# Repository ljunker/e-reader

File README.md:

# DIY e-reader

A pocket e-reader built around a **Waveshare 4.2" e-Paper Module V2** (400 × 300, black/white + 4 grays),
an **ESP32-S3** (Unexpected Maker FeatherS3[D], 16 MB flash / 8 MB PSRAM), a microSD card and a 3D-printed case.
It reads books in portrait at 300 × 400, sleeps between page turns and runs for weeks on a 1500–2000 mAh LiPo.

| | |
|---|---|
| **Formats** | `.txt`; **EPUB** laid out on the device (bold/italic, headings, pictures, table of contents); **PDF / comics** pre-rendered on your computer with [`xtconvert`](tools/converter) into `.xtp` |
| **Controls** | PREV / NEXT on the grip edge (left by default, `left_handed` in `cad/params.scad`), MENU / OK / BACK below the screen; long press jumps 10 pages |
| **Getting books on** | microSD card, Wi‑Fi upload page in the browser, USB drive over USB‑C, or straight from an OPDS catalog (Calibre content server, Project Gutenberg …) |
| **Case** | ~95 × 137 × 17 mm, parametric OpenSCAD, fits a Bambu A1 mini |

## Repository
| Folder | What's inside |
|---|---|
| [`hardware/`](hardware) | [Bill of materials](hardware/BOM.md), [wiring](hardware/wiring.md) |
| [`cad/`](cad) | OpenSCAD case: `params.scad` holds every dimension; `make` exports STLs and runs a collision check |
| [`firmware/`](firmware) | PlatformIO project (Arduino on ESP32-S3) |
| [`tools/converter/`](tools/converter) | `xtconvert`: PDF / CBZ / images → `.xtp` |
| [`docs/`](docs) | [Assembly](docs/assembly.md), [printing](docs/printing.md) |

## Quick start
1. Buy the parts in the [BOM](hardware/BOM.md) and wire them per [wiring.md](hardware/wiring.md) (breadboard first).
2. Flash the firmware:
   ```bash
   cd firmware && pio run -t upload
   ```
3. Format a microSD card as FAT32, make a `books/` folder and copy `.epub` and `.txt` files and converted PDFs into it:
   ```bash
   cd tools/converter && uv run xtconvert ~/Downloads/paper.pdf --mode width -o /Volumes/SD/books/
   ```
4. Measure your display module, set the values in `cad/params.scad`, print the fit test, then the case ([printing.md](docs/printing.md)).
5. Assemble ([assembly.md](docs/assembly.md)).

## Development
```bash
cd firmware && pio test -e native          # panel model, layout, EPUB, zip, image and .xtp unit tests on your computer
cd tools/converter && uv run pytest        # converter tests
make -C cad                                # STLs + collision check (needs OpenSCAD 2024+)
make -C cad png                            # preview renders
make -C cad steps                          # step-by-step pictures for docs/assembly.md
```

## Simulator
Try the firmware in the browser, without hardware:
```bash
brew install emscripten                 # once (or https://emscripten.org)
cd firmware && pio run -e sim -t serve  # then open http://localhost:8000/
```
`env:sim` compiles everything in `src/` unchanged, with the real GxEPD2, Adafruit GFX and U8g2 libraries
and String/FS from the arduino-esp32 core, to WebAssembly. Only the hardware underneath is simulated (`firmware/sim/`):
- **Display:** an SSD1683 model (`lib/epdsim`) receives GxEPD2's SPI commands and the reader's 4-gray refresh. It holds
  BUSY for the real refresh time and shows full refreshes flashing, like the panel does. "Instant refresh" skips the wait.
- **Buttons:** click the caps or use the keys ← PREV, → NEXT, M MENU, Enter OK, Esc BACK. Holding a button gives a
  long press.
- **microSD and NVS:** kept in the browser's IndexedDB. On first start the card gets the test EPUBs, a short TXT and a
  `wifi.txt`. The side panel lists, adds, downloads and deletes files.
- **Deep sleep:** "Skip 3 min" runs out the idle timer. The panel keeps its picture, and a button reboots the
  firmware with its RTC memory, as on the chip. "Reset" is a cold start.
- **USB-C:** set the cable to Unplugged, Computer or Charger. While the drive is on, the file panel is the computer's
  view, and "Eject" ejects it.
- **Wi‑Fi:** the firmware's own upload page appears in the side panel. A service worker passes its requests to the
  firmware's web server.
- **Online library:** the card gets an `opds.txt` for a demo catalog of the sample books that `serve.py` serves,
  behind Digest login like Calibre (user and password `demo`). The firmware's HTTP requests go through
  `serve.py`'s `/proxy`, so real catalogs (your Calibre server, Gutenberg) work too. "Edit opds.txt" changes the list.
- **Battery:** a simulated MAX17048 on I2C, set with the slider.

Not simulated: radio, real USB/sector access, RAM/PSRAM limits and the speed of the ESP32-S3 (EPUB conversion is
much faster in the browser).

## EPUB on the device
The first time a book is opened, the reader converts it once into cache files in `/.reader/` on the card
(this takes a few seconds to about a minute with many pictures; the panel shows the progress).
After that, opening, turning pages and changing the font size are as fast as with `.txt` files.
MENU → **Contents** jumps to a chapter.

**Hyphenation:** copy the [`sdcard/hyph/`](sdcard/hyph) folder to the top of the card (`/hyph/de.hyp`, `/hyph/en.hyp`).
Long words are then broken at line ends, so justified lines get even gaps. The language comes from the EPUB's
`dc:language`; for TXT files and EPUBs without it the reader guesses German or English from the text. Other
languages and a card without `/hyph/` still break after hyphens already in a word ("E-Mail-Adresse").
MENU → **Hyphenation** switches it off. Built with `xtconvert hyph` from the hyph-utf8 patterns in
`tools/converter/patterns/`. Updating to this firmware converts each EPUB once more on first open.

**Fonts:** copy the [`sdcard/fonts/`](sdcard/fonts) folder to the top of the card (`/fonts/literata.xff`).
Books are then set in Literata (regular, bold, italic, bold italic) with true quotes and dashes; menus always use the
built-in Inter, which also stands in for books when the card has no fonts. MENU → **Font** switches between the
families in `/fonts/`. Your own TTF/OTF fonts: `xtconvert font` ([tools/converter](tools/converter#fonts)).

Supported: EPUB 2 and 3, chapters in reading order, headings, bold and italic, alignment, blockquotes,
lists, line breaks, page breaks from CSS, JPEG (baseline) and PNG pictures dithered to the panel,
and the table of contents from the nav document or the NCX.
Not supported: DRM-protected books (the reader says so), GIF/SVG and progressive JPEG pictures (left out),
characters outside Latin-1 and the usual punctuation (shown as the nearest Latin letter or `?`), footnote pop-ups.

## Wi‑Fi upload & USB drive
**Wi‑Fi:** put a `wifi.txt` in the top folder of the card, one network per line:
```
# SSID = password   (lines starting with # are ignored)
Zuhause = geheim123
Büro WLAN = pass=word
Gartenhaus =
```
The line is split at the first `=`, so the password may contain `=` or `#`; leave it empty for an open network.
MENU → **Wi‑Fi upload** joins the strongest of these networks and shows the address.
Open `http://ereader.local/` (or the IP shown) in a browser on the same network to upload, replace or delete books;
the screen counts the files that arrive. BACK switches Wi‑Fi off, and so do 10 minutes without a request.

**USB:** plug the reader into a computer with the USB‑C cable. It asks whether to show the card as a USB drive
(OK) or to keep reading (BACK); MENU → **USB drive** offers it again. Copy books into `books/`, eject the drive,
and the reader returns to the library. A charger alone never triggers the question.

The firmware uses its own partition table (`firmware/partitions-16MB.csv`: two 4 MB app slots, TinyUF2, FAT); the first
`pio run -t upload` after updating rewrites it. Saved reading positions stay.

## Online library (OPDS / Calibre)
Browse an OPDS catalog on the reader and download books straight into `books/`. Put an `opds.txt` next to
`wifi.txt` in the top folder of the card, one catalog per line:
```
# Name = URL   (user and password go into the URL; add "insecure" for a self-signed HTTPS server)
Calibre = http://leser:geheim@192.168.1.10:8080/opds
Project Gutenberg = https://www.gutenberg.org/ebooks.opds/
```
MENU → **Online library** joins the Wi‑Fi from `wifi.txt` and opens the catalog (with several, it asks which).
PREV/NEXT move, OK opens a folder or a book, BACK goes up a level and, at the top, switches Wi‑Fi off; MENU
leaves straight away. A book shows its author, size and description; OK downloads it as
`books/<Title> - <Author>.epub` (or `.txt`), and OK again opens it. "More …" at the end of a list loads the next
page. Ten minutes without a button switch Wi‑Fi off.

**Calibre:** start the content server (Preferences → Sharing over the net, or
`calibre-server --listen-on 0.0.0.0 ~/Calibre\ Library`); the catalog is at `http://<computer>:8080/opds`.
With "Require username and password" on, put them into the URL as above (percent-encode `@`, `:` and `/` in
them). Both of Calibre's login methods work (Digest over HTTP, Basic over HTTPS). The reader sends them only to the
catalog's own server, and only after it asks.

Works with OPDS 1.x (Atom) catalogs; EPUB is taken first, then plain text. Books offered only as MOBI, PDF or
AZW are listed but cannot be downloaded. No search (there is no keyboard), and OPDS 2 (JSON) catalogs are not supported.

## Status / roadmap
- [x] Hardware design, wiring, BOM
- [x] Parametric case with collision check
- [x] PDF/comic converter and `.xtp` format
- [x] Firmware: display, buttons, SD, deep sleep + wake on any button, library, TXT reader with justified text and cached pagination, `.xtp` viewer, font sizes, saved positions
- [ ] Bring-up on real hardware (FeatherS3[D] pin check, Rev2.2 `PWR` pin, rotation, fuel gauge, card detect polarity)
- [x] Fonts generated from TTFs (`xtconvert font`, loaded from the card), shown in black and white
- [x] Hyphenation (Liang patterns, German and English)
- [x] EPUB (unzip, OPF/spine, XHTML + CSS subset, images, table of contents)
- [x] True 4-gray refresh for `.xtp` pages and the sleep-screen cover (about 5.5 s per refresh)
- [x] Wi‑Fi upload page, USB mass storage
- [x] Online library: OPDS catalogs (Calibre content server) over HTTP and HTTPS
- [ ] Optional KiCad carrier PCB (draft in tag `carrier-pcb-draft`)

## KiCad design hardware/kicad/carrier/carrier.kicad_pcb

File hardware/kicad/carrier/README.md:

# Carrier board

A 2-layer board (88.5 × 130 mm, 1.6 mm) that replaces the hand wiring. It takes the
place of the old chassis plate: it sits behind the display, clamped between the
front frame's screw bosses and the back shell.

| Back side (towards the back shell) | Front side (towards the display) |
|---|---|
|  |  |

- **Back side:** FeatherS3 on plain pin headers, microSD socket (card goes in through the
  right side wall), page-turn buttons at the right edge, power switch (top edge),
  battery connector, 1×9 header for the display cable.
- **Front side:** MENU / OK / BACK buttons under the screen.
- GND pour on both layers, 0.25 mm signal and 0.5 mm power tracks, nothing finer than 0.15 mm.
- The GPIO assignment is the same as in [`wiring.md`](../../wiring.md), so the firmware is unchanged.

## Ordering (JLCPCB or similar)
Upload [`fab/carrier-gerbers.zip`](fab/carrier-gerbers.zip). Settings: 2 layers, 1.6 mm FR-4,
HASL lead-free or ENIG, any solder mask colour; all other settings default. No assembly
needed; everything is hand-solderable. Parts: [`fab/carrier-bom.csv`](fab/carrier-bom.csv)
and the [project BOM](../../BOM.md).

Schematic: [`fab/carrier-schematic.pdf`](fab/carrier-schematic.pdf).
3D model for checking against the case: `fab/carrier.step`.

## Soldering order
1. microSD socket J1 (1.1 mm pitch; tack one shield pad, align, then the rest), R1–R5, C1, C2.
2. Front buttons SW1–SW3 on the **front** side, side buttons SW4/SW5, power switch SW6,
   battery connector J2, display header J3 on the **back** side.
3. FeatherS3: put the 16- and 12-pin headers into the board (plastic spacer on the back side),
   put the Feather on top and solder both ends.
4. Trim all through-hole leads on the **display side** to ≤ 1 mm and cover them with Kapton
   tape. The display sits 3 mm away.

## Before ordering, check against the real parts
- **microSD orientation:** the card is assumed to go in on the footprint's +Y side (Molex 104031-0811).
  Compare with the datasheet drawing.
- **Side buttons:** `side_act_h` (actuator height above the board, 3.5 mm) in `cad/params.scad`
  must match the switch you buy. It sets the height of the button holes.
- **FeatherS3 header:** the two Feather pins that the board leaves unused (3 and 16) are only
  marked "unconnected" here, so their exact function on the FeatherS3 doesn't matter.

## Regenerating
Everything is generated from [`design.py`](design.py) (parts, nets, placement) and
`cad/params.scad` (outline, button and connector positions). Don't edit the KiCad files by hand;
change the sources and run:

```bash
make            # place + autoroute (Freerouting), schematic, ERC/DRC/parity check, fab outputs
make pcb        # only place + route
make check      # ERC, DRC with schematic parity
```

Needs KiCad 10 (its bundled Python runs `generate_pcb.py` and `route.py`), Java 17+ and the
GitHub CLI (fetches Freerouting into `.tools/` on first use). Freerouting's result varies
between runs, so `route.py` retries up to 5 times until KiCad reports every connection made.

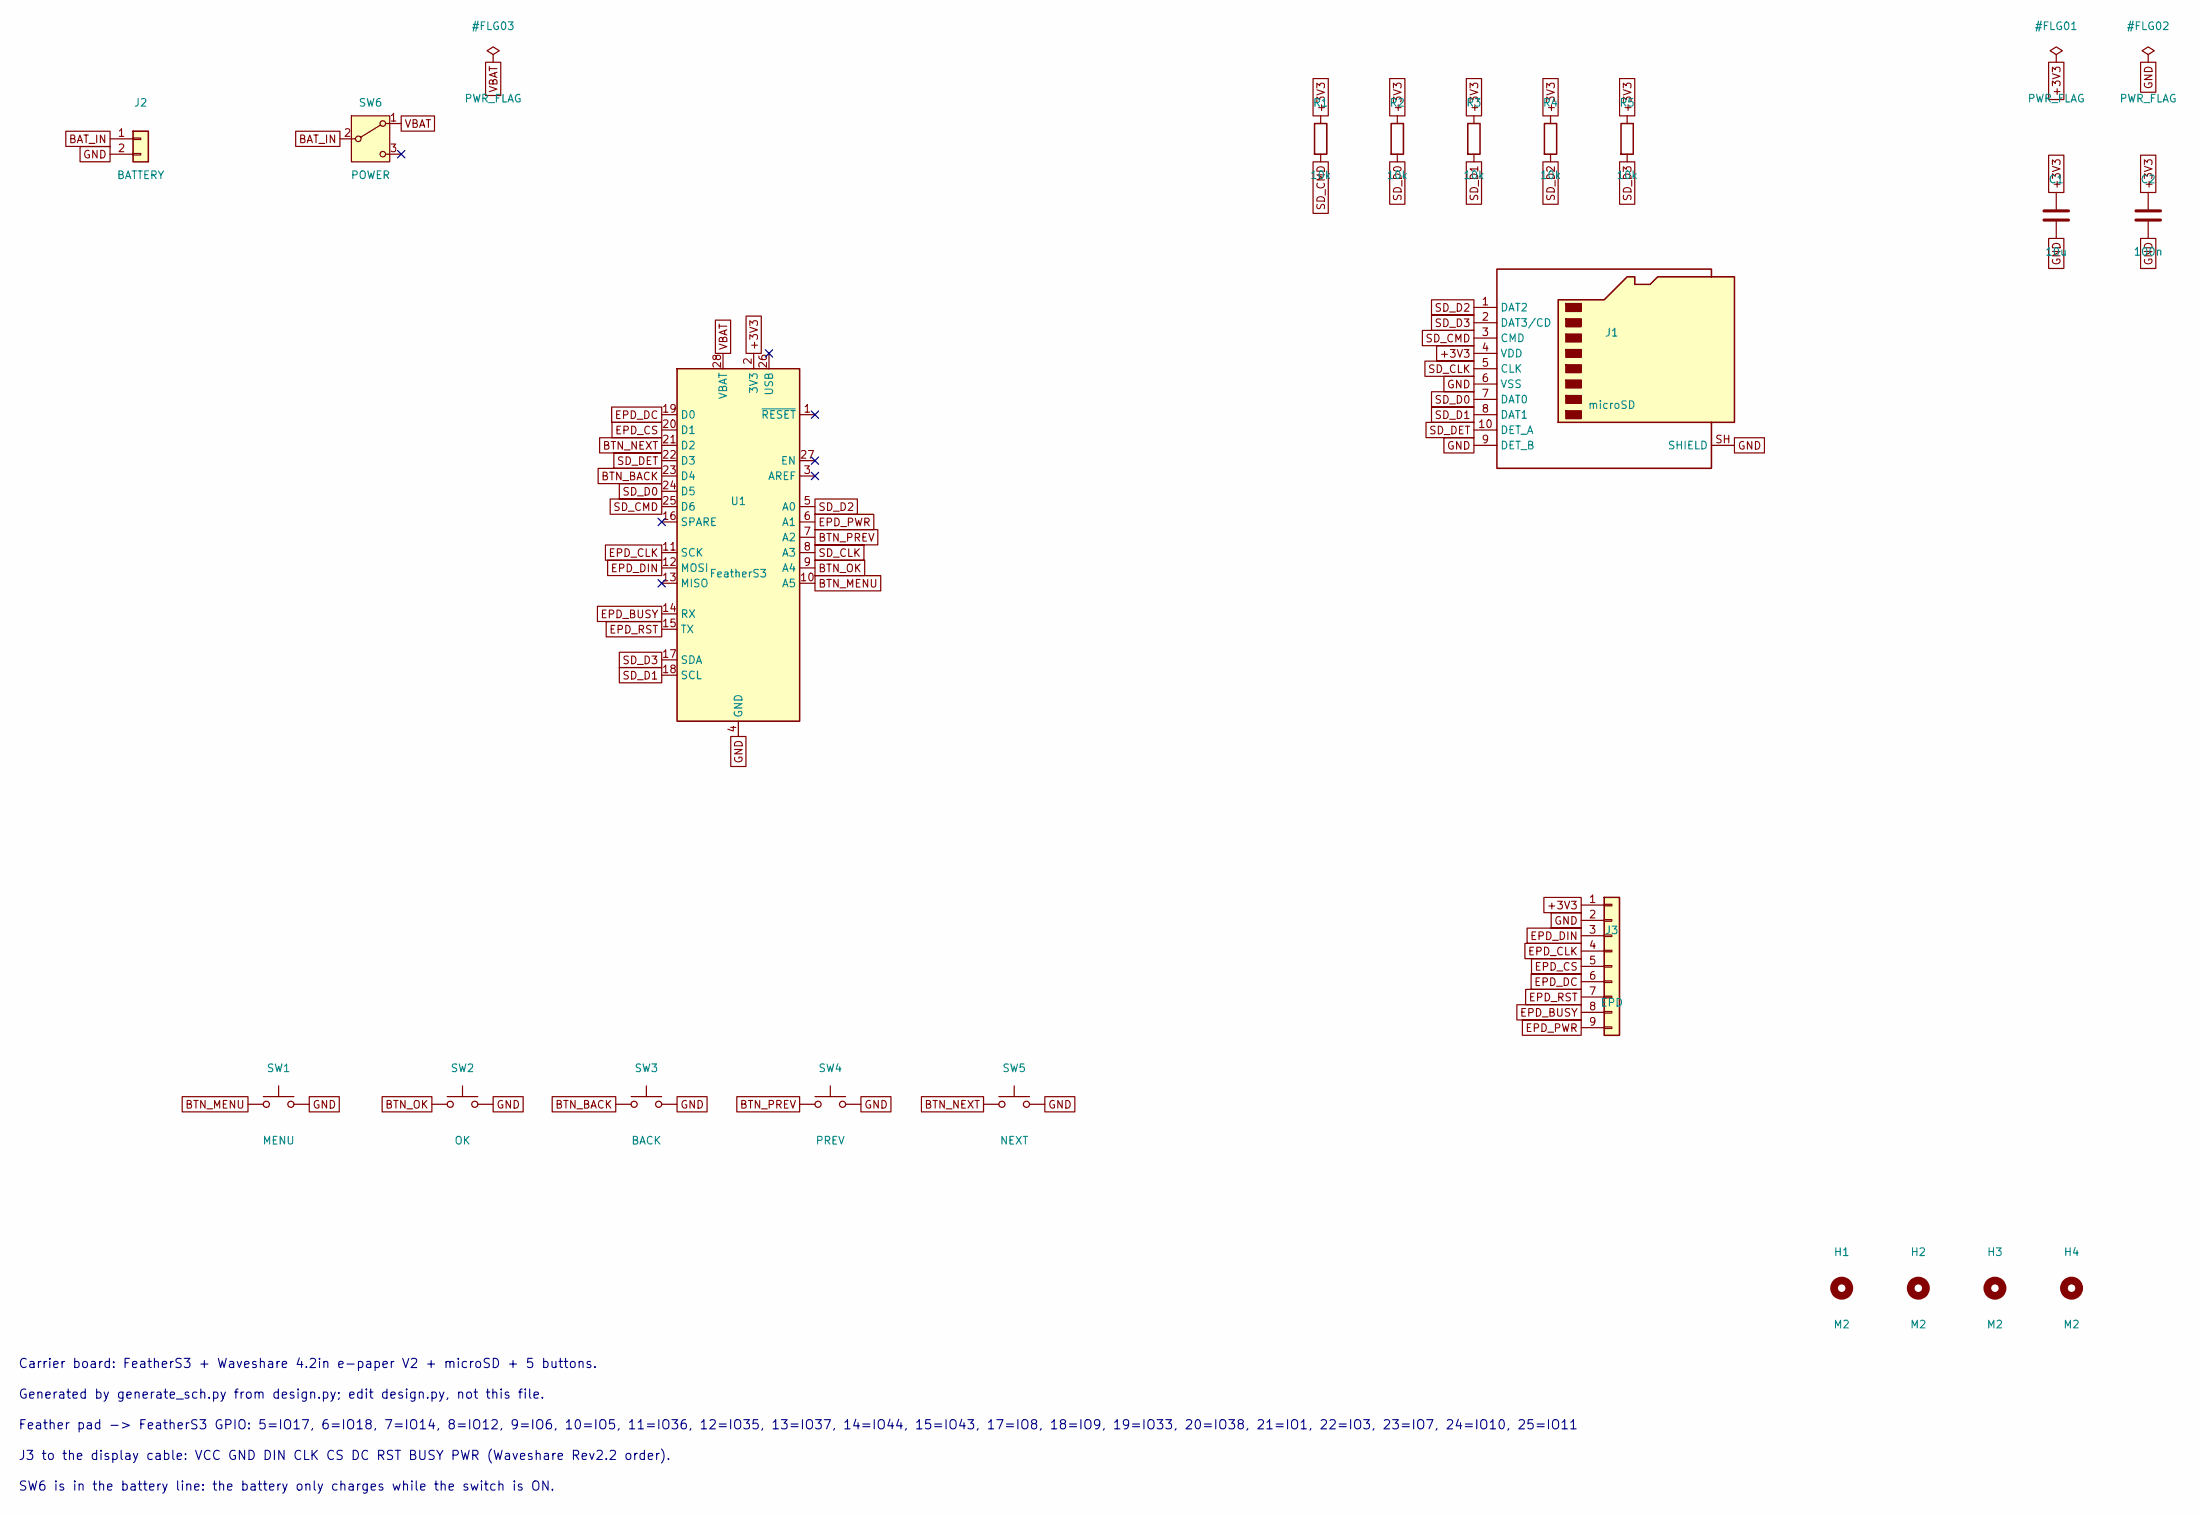
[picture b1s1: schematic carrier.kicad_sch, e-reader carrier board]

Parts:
C1: 10u; C_0805_2012Metric; MPN 0805 10 µF 10 V X5R
C2: 100n; C_0805_2012Metric; MPN 0805 100 nF 50 V X7R
H1, H2, H3, H4: M2; MountingHole_2.2mm_M2
J1: microSD; microSD_HC_Molex_104031-0811; MPN Molex 104031-0811
J2: BATTERY; JST_PH_S2B-PH-K_1x02_P2.00mm_Horizontal; MPN JST S2B-PH-K-S
J3: EPD; PinHeader_1x09_P2.54mm_Horizontal; MPN 1×9 right-angle pin header 2.54 mm (or 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
R1, R2, R3, R4, R5: 10k; R_0805_2012Metric; MPN 0805 10 kΩ 1 %
SW1: MENU; SW_PUSH_6mm_H4.3mm; MPN 6×6 mm tactile, 4.3 mm (e.g. PHAP3301)
SW2: OK; SW_PUSH_6mm_H4.3mm; MPN 6×6 mm tactile, 4.3 mm (e.g. PHAP3301)
SW3: BACK; SW_PUSH_6mm_H4.3mm; MPN 6×6 mm tactile, 4.3 mm (e.g. PHAP3301)
SW4: PREV; SW_Tactile_SPST_Angled_PTS645Vx31-2LFS; MPN C&K PTS645VL31-2 LFS (right angle)
SW5: NEXT; SW_Tactile_SPST_Angled_PTS645Vx31-2LFS; MPN C&K PTS645VL31-2 LFS (right angle)
SW6: POWER; SW_Slide_SPDT_Angled_CK_OS102011MA1Q; MPN C&K OS102011MA1QN1
U1: FeatherS3; Adafruit_Feather; MPN Unexpected Maker FeatherS3 + 2× pin hea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

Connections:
+3V3: C1.1, C2.1, J1.4 (VDD), J3.1, R1.1, R2.1, R3.1, R4.1, R5.1, U1.2 (3V3)
BAT_IN: J2.1, SW6.2 (B)
BTN_BACK: SW3.1, U1.23 (D4)
BTN_MENU: SW1.1, U1.10 (A5)
BTN_NEXT: SW5.1, U1.21 (D2)
BTN_OK: SW2.1, U1.9 (A4)
BTN_PREV: SW4.1, U1.7 (A2)
EPD_BUSY: J3.8, U1.14 (RX)
EPD_CLK: J3.4, U1.11 (SCK)
EPD_CS: J3.5, U1.20 (D1)
EPD_DC: J3.6, U1.19 (D0)
EPD_DIN: J3.3, U1.12 (MOSI)
EPD_PWR: J3.9, U1.6 (A1)
EPD_RST: J3.7, U1.15 (TX)
GND: C1.2, C2.2, J1.6 (VSS), J1.9 (DET_B), J1.SH (SHIELD), J2.2, J3.2, SW1.2, SW2.2, SW3.2, SW4.2, SW5.2, U1.4 (GND)
SD_CLK: J1.5 (CLK), U1.8 (A3)
SD_CMD: J1.3 (CMD), R1.2, U1.25 (D6)
SD_D0: J1.7 (DAT0), R2.2, U1.24 (D5)
SD_D1: J1.8 (DAT1), R3.2, U1.18 (SCL)
SD_D2: J1.1 (DAT2), R4.2, U1.5 (A0)
SD_D3: J1.2 (DAT3/CD), R5.2, U1.17 (SDA)
SD_DET: J1.10 (DET_A), U1.22 (D3)
VBAT: SW6.1 (A), U1.28 (VBAT)

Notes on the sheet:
Carrier board: FeatherS3 + Waveshare 4.2in e-paper V2 + microSD + 5 buttons.
Generated by generate_sch.py from design.py; edit design.py, not this file.
Feather pad -> FeatherS3 GPIO: 5=IO17, 6=IO18, 7=IO14, 8=IO12, 9=IO6, 10=IO5, 11=IO36, 12=IO35, 13=IO37, 14=IO44, 15=IO43, 17=IO8, 18=IO9, 19=IO33, 20=IO38, 21=IO1, 22=IO3, 23=IO7, 24=IO10, 25=IO11
J3 to the display cable: VCC GND DIN CLK CS DC RST BUSY PWR (Waveshare Rev2.2 order).
SW6 is in the battery line: the battery only charges while the switch is ON.

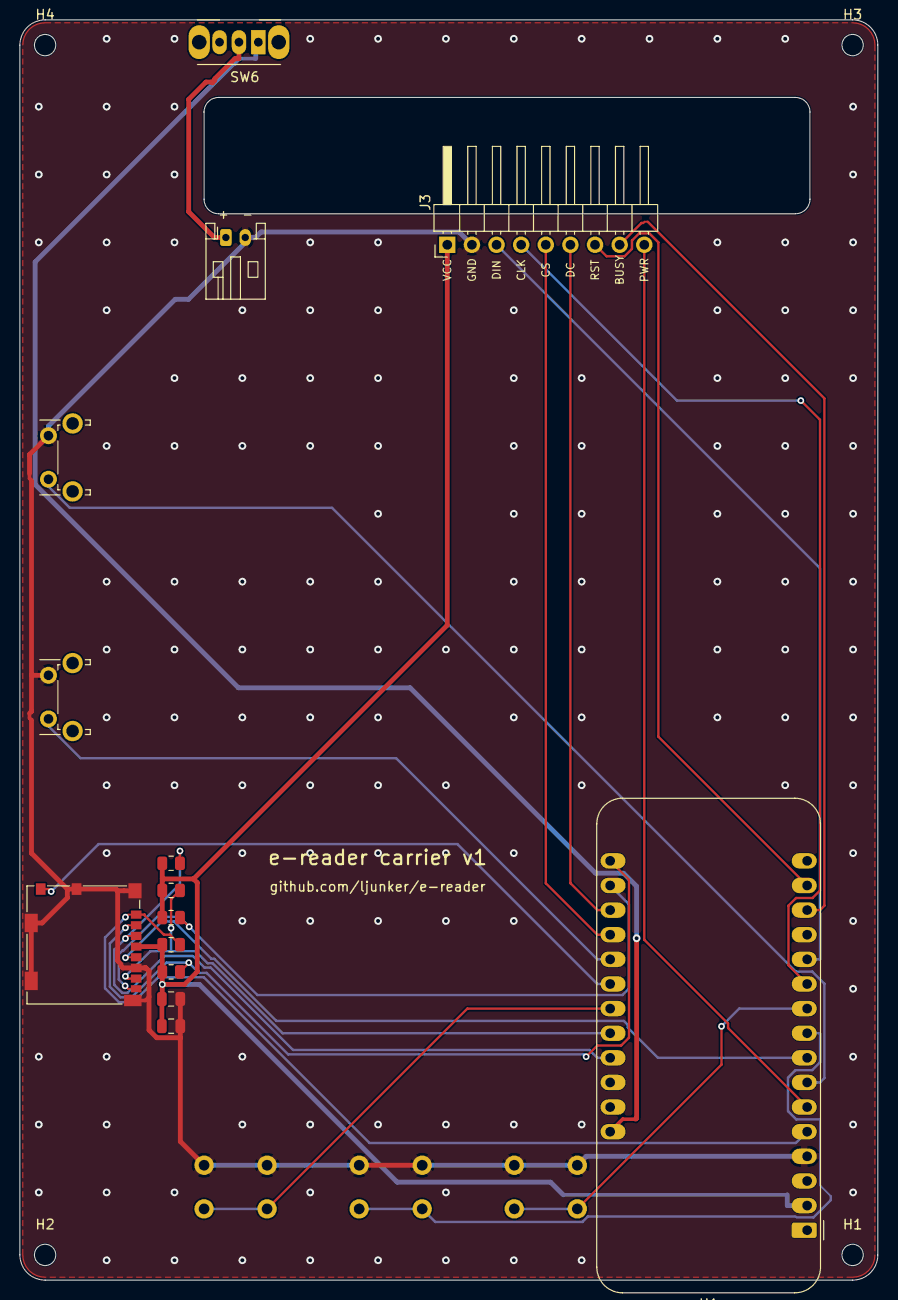
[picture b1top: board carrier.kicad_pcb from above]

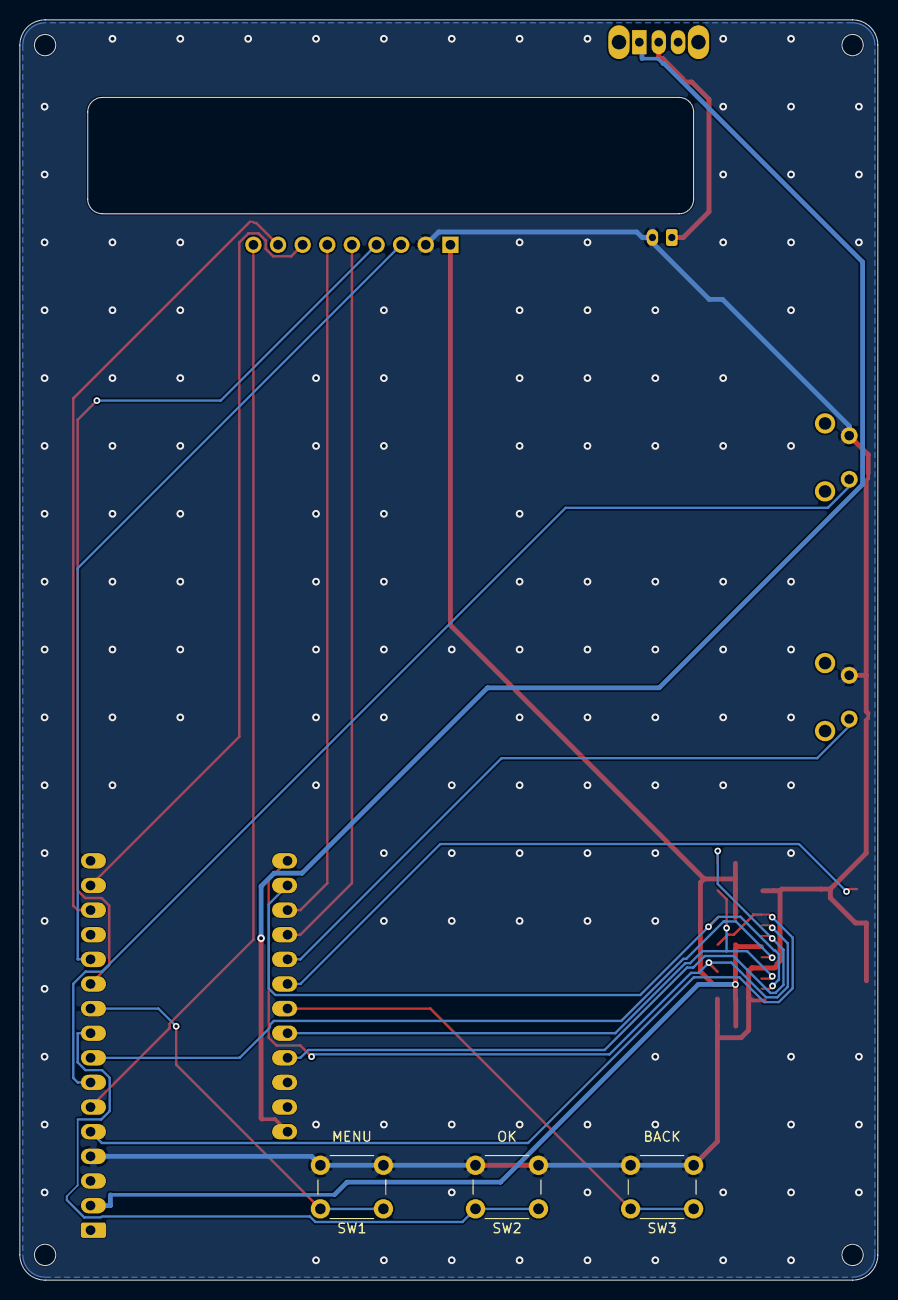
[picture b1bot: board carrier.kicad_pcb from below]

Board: 2 copper layers, 88.5 x 130.0 mm, 21 parts (3 on the bottom side), 23 nets.

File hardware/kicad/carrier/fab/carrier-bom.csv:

"Refs","Value","Footprint","Part","Qty"
"C1","10u","Capacitor_SMD:C_0805_2012Metric","0805 10 µF 10 V X5R","1"
"C2","100n","Capacitor_SMD:C_0805_2012Metric","0805 100 nF 50 V X7R","1"
"J1","microSD","Connector_Card:microSD_HC_Molex_104031-0811","Molex 104031-0811","1"
"J2","BATTERY","Connector_JST:JST_PH_S2B-PH-K_1x02_P2.00mm_Horizontal","JST S2B-PH-K-S","1"
"J3","EPD","Connector_PinHeader_2.54mm:PinHeader_1x09_P2.54mm_Horizontal","1×9 right-angle pin header 2.54 mm (or solder the cable directly)","1"
"R1,R2,R3,R4,R5","10k","Resistor_SMD:R_0805_2012Metric","0805 10 kΩ 1 %","5"
"SW1","MENU","Button_Switch_THT:SW_PUSH_6mm_H4.3mm","6×6 mm tactile, 4.3 mm (e.g. PHAP3301)","1"
"SW2","OK","Button_Switch_THT:SW_PUSH_6mm_H4.3mm","6×6 mm tactile, 4.3 mm (e.g. PHAP3301)","1"
"SW3","BACK","Button_Switch_THT:SW_PUSH_6mm_H4.3mm","6×6 mm tactile, 4.3 mm (e.g. PHAP3301)","1"
"SW4","PREV","Button_Switch_THT:SW_Tactile_SPST_Angled_PTS645Vx31-2LFS","C&K PTS645VL31-2 LFS (right angle)","1"
"SW5","NEXT","Button_Switch_THT:SW_Tactile_SPST_Angled_PTS645Vx31-2LFS","C&K PTS645VL31-2 LFS (right angle)","1"
"SW6","POWER","Button_Switch_THT:SW_Slide_SPDT_Angled_CK_OS102011MA1Q","C&K OS102011MA1QN1","1"
"U1","FeatherS3","Module:Adafruit_Feather","Unexpected Maker FeatherS3 + 2× pin header (16 + 12)","1"

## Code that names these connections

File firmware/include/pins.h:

#pragma once
// Pin map for the Unexpected Maker FeatherS3[D] (16 MB flash, 8 MB QSPI PSRAM).
// See hardware/wiring.md. Change pins here only.
//
// The board breaks out 21 GPIOs. SDA/SCL (IO8/IO9) also go to the on-board
// MAX17048 fuel gauge, so 19 remain for 19 signals. The octal-PSRAM pins of
// other S3 modules (IO33-IO37) are free here, the PSRAM is a separate QSPI chip.
//
// Buttons and card detect sit on RTC GPIOs (IO0-IO21) so the buttons can wake
// the chip from deep sleep. IO0 is also the BOOT button: holding BACK while
// pressing RESET starts the ROM bootloader.

// ---- Waveshare 4.2" V2 e-paper (SPI2) ----
#define PIN_EPD_SCK   36   // SCK
#define PIN_EPD_MOSI  35   // MO
#define PIN_EPD_CS    44   // RX
#define PIN_EPD_DC    43   // TX
#define PIN_EPD_RST   37   // MI
#define PIN_EPD_BUSY  38   // 38
#define PIN_EPD_PWR   33   // 33; Rev2.2 power enable, -1 if your module has no PWR pin

// ---- microSD (SDMMC, 4-bit, any GPIO via the matrix) ----
#define PIN_SD_CLK    17   // 17
#define PIN_SD_CMD    18   // 18
#define PIN_SD_D0     14   // 14
#define PIN_SD_D1     12   // 12
#define PIN_SD_D2     6    // 6
#define PIN_SD_D3     5    // 5
#define PIN_SD_DET    3    // 3; -1 if not wired (a missing card then shows as a mount error)
#define SD_DET_ACTIVE HIGH // Adafruit 4682: DET is shorted to GND without a card, pulled up with one

// ---- buttons (active low, RTC GPIOs so they can wake from deep sleep) ----
#define PIN_BTN_PREV  11   // 11
#define PIN_BTN_NEXT  10   // 10
#define PIN_BTN_MENU  7    // 7
#define PIN_BTN_OK    1    // 1
#define PIN_BTN_BACK  0    // 0 (BOOT button)

// ---- on-board ----
#define PIN_I2C_SDA     8    // MAX17048 fuel gauge (I2C1 STEMMA QT, on the always-on LDO1)
#define PIN_I2C_SCL     9
#define PIN_LDO2        39   // high = LDO2 on: RGB LED and the I2C2 STEMMA QT; kept low to save power
#define PIN_LED         13   // blue LED, kept off
#define PIN_VBUS_SENSE  34   // high = 5 V present on USB-C
#define PIN_RF_SWITCH   41   // low = on-board antenna, high = u.FL
#define PIN_LIGHT_SENSE 4    // ambient light sensor (analog), not used yet
